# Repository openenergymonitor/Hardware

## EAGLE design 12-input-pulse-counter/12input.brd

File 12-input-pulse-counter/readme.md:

## 12 Input Pulse Counter

**This is a design in development for a 12-input puse counter for interfacing with 12 utility meters.**

Many meters have pulse outputs, including electricity meters: single phase, 3-phase, import, export.. Gas meters, Water flow meters etc

The pulse output may be a flashing LED or a switching relay (usually solid state) or both.

In the case of an electricity meter a pulse output corresponds to a certain amount of energy passing through the meter (Kwhr/Wh). For single-phase domestic electricity meters (eg. Elster A100c) each pulse usually corresponds to 1 Wh (1000 pulses per kwh).  For the case of higher power meters (often three-phase) each pulse corresponds to a greater amount of energy eg. 2whr per pulse or even 10whr per pulse. 

Full introduction to pulse counting: [Building Blocks > Pulse counting](http://openenergymonitor.org/emon/buildingblocks/introduction-to-pulse-counting)

The usual way to do pulse counting on the Arduino is to use the 2 Interrupt pins but this limits us to 2 meters. The following hardware design is for a 12 input arduino based pulse counter that runs firmware that samples all the arduino digital input pins at high sample rate. For full details including arduino source code see: [Building Blocks > 12 input pulse counting](http://openenergymonitor.org/emon/buildingblocks/12-input-pulse-counting)

### Eagle schematic and board file

Download both the schematic and board file and open in eagle, click on File > Switch to Board to navigate between schematic view and PCB Board view.

- Schematic: [12input.sch](12input.sch)
- Board: [12input.brd](12input.brd)

### Schematic

### Board

### Open Hardware

Hardware designs (schematics and CAD) files are licensed under the [Creative Commons Attribution-ShareAlike 3.0 Unported License](http://creativecommons.org/licenses/by-sa/3.0/) and follow the terms of the [OSHW (Open-source hardware) Statement of Principles 1.0.](http://freedomdefined.org/OSHW)

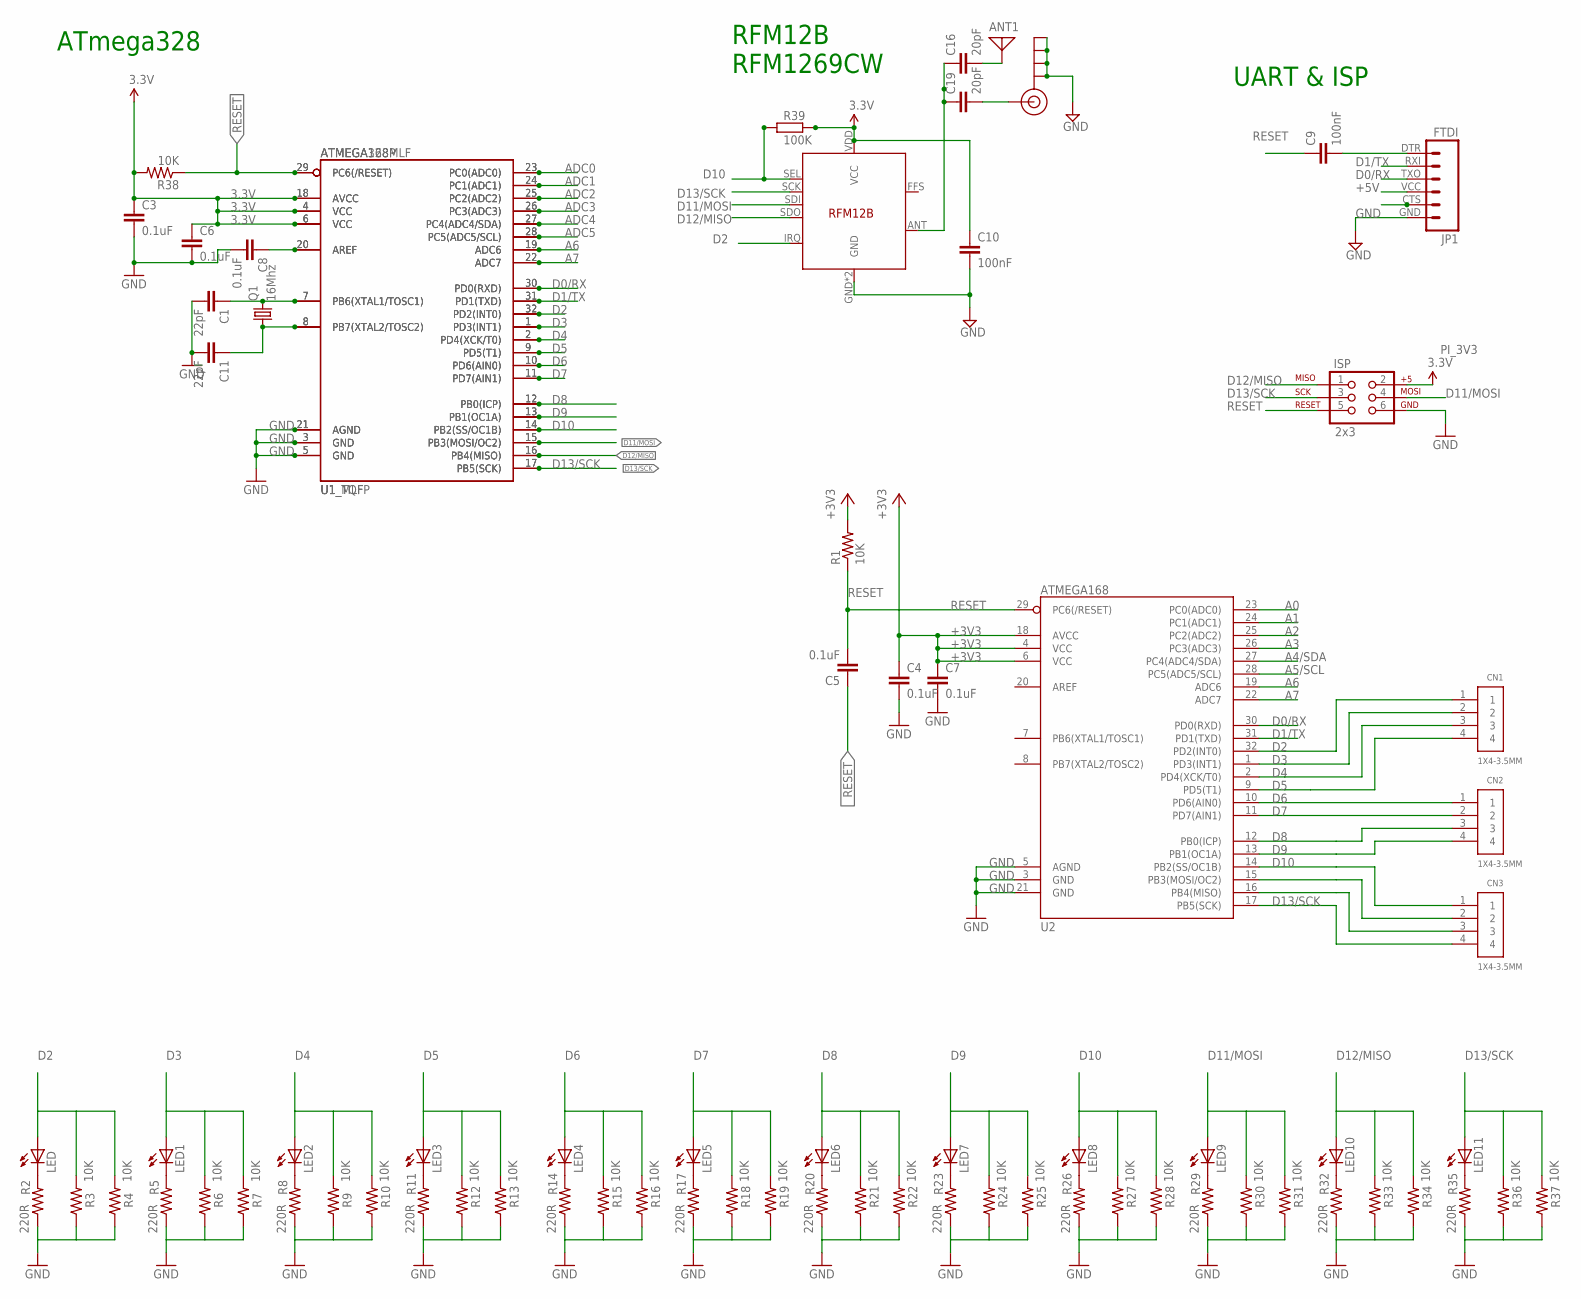
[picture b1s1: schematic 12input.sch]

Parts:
ANT1: ANTENNA; PAD-01
C1, C11: 22pF; C0603
C3, C4, C5, C6, C7, C8: 0.1uF; C0603
C9, C10: 100nF; C0603
C16, C19: 20pF; C0603
CN1, CN2, CN3: 1X4-3.5MM; 1X04-3.5MM
ISP: 2x3; 2X3
J$1: SMA_EDGE; SMA-EDGE
JP1: FTDI; FTDI_BASIC
LED, LED1, LED2, LED3, LED4, LED5, LED6, LED7, LED8, LED9, LED10, LED11: LEDSML0603; SML0603
Q1: 16Mhz; HC49UP
R1, R3, R6, R9, R12, R15, R18, R21, R24, R27, R30, R33, R36, R38: 10K; R0603
R2, R5, R8, R11, R14, R17, R20, R23, R26, R29, R32, R35: 220R; R0603
R4, R7, R10, R13, R16, R19, R22, R25, R28, R31, R34, R37: 10K; 0204/7
R39: 100K; R0603
U1_MLF: ATMEGA168MLF; MLF32
U1_TQFP: ATMEGA328P; TQFP32-08
U2: ATMEGA168; TQFP32-08
U$14: RFM12B

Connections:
3.3V: C3.1, C6.1, C10.1, ISP.2, R38.2, R39.2, U1_MLF.4 (VCC), U1_MLF.6 (VCC), U1_MLF.18 (AVCC), U1_TQFP.4 (VCC), U1_TQFP.6 (VCC), U1_TQFP.18 (AVCC), U$14.VDD (VCC)
+3V3: C4.1, C7.1, R1.2, U2.4 (VCC), U2.6 (VCC), U2.18 (AVCC)
+5V: JP1.VCC (4)
A0: U2.23 (PC0(ADC0))
A1: U2.24 (PC1(ADC1))
A2: U2.25 (PC2(ADC2))
A3: U2.26 (PC3(ADC3))
A4/SDA: U2.27 (PC4(ADC4/SDA))
A5/SCL: U2.28 (PC5(ADC5/SCL))
A6: U1_MLF.19 (ADC6), U1_TQFP.19 (ADC6), U2.19 (ADC6)
A7: U1_MLF.22 (ADC7), U1_TQFP.22 (ADC7), U2.22 (ADC7)
ADC0: U1_MLF.23 (PC0(ADC0)), U1_TQFP.23 (PC0(ADC0))
ADC1: U1_MLF.24 (PC1(ADC1)), U1_TQFP.24 (PC1(ADC1))
ADC2: U1_MLF.25 (PC2(ADC2)), U1_TQFP.25 (PC2(ADC2))
ADC3: U1_MLF.26 (PC3(ADC3)), U1_TQFP.26 (PC3(ADC3))
ADC4: U1_MLF.27 (PC4(ADC4/SDA)), U1_TQFP.27 (PC4(ADC4/SDA))
ADC5: U1_MLF.28 (PC5(ADC5/SCL)), U1_TQFP.28 (PC5(ADC5/SCL))
D0/RX: JP1.TXO (3), U1_MLF.30 (PD0(RXD)), U1_TQFP.30 (PD0(RXD)), U2.30 (PD0(RXD))
D1/TX: JP1.RXI (2), U1_MLF.31 (PD1(TXD)), U1_TQFP.31 (PD1(TXD)), U2.31 (PD1(TXD))
D2: CN1.1, LED.A, R3.2, R4.2, U1_MLF.32 (PD2(INT0)), U1_TQFP.32 (PD2(INT0)), U2.32 (PD2(INT0)), U$14.IRQ
D3: CN1.2, LED1.A, R6.2, R7.2, U1_MLF.1 (PD3(INT1)), U1_TQFP.1 (PD3(INT1)), U2.1 (PD3(INT1))
D4: CN1.3, LED2.A, R9.2, R10.2, U1_MLF.2 (PD4(XCK/T0)), U1_TQFP.2 (PD4(XCK/T0)), U2.2 (PD4(XCK/T0))
D5: CN1.4, LED3.A, R12.2, R13.2, U1_MLF.9 (PD5(T1)), U1_TQFP.9 (PD5(T1)), U2.9 (PD5(T1))
D6: CN2.1, LED4.A, R15.2, R16.2, U1_MLF.10 (PD6(AIN0)), U1_TQFP.10 (PD6(AIN0)), U2.10 (PD6(AIN0))
D7: CN2.2, LED5.A, R18.2, R19.2, U1_MLF.11 (PD7(AIN1)), U1_TQFP.11 (PD7(AIN1)), U2.11 (PD7(AIN1))
D8: CN2.3, LED6.A, R21.2, R22.2, U1_MLF.12 (PB0(ICP)), U1_TQFP.12 (PB0(ICP)), U2.12 (PB0(ICP))
D9: CN2.4, LED7.A, R24.2, R25.2, U1_MLF.13 (PB1(OC1A)), U1_TQFP.13 (PB1(OC1A)), U2.13 (PB1(OC1A))
D10: CN3.1, LED8.A, R27.2, R28.2, R39.1, U1_MLF.14 (PB2(SS/OC1B)), U1_TQFP.14 (PB2(SS/OC1B)), U2.14 (PB2(SS/OC1B)), U$14.SEL
D11/MOSI: CN3.2, ISP.4, LED9.A, R30.2, R31.2, U1_MLF.15 (PB3(MOSI/OC2)), U1_TQFP.15 (PB3(MOSI/OC2)), U2.15 (PB3(MOSI/OC2)), U$14.SDI
D12/MISO: CN3.3, ISP.1, LED10.A, R33.2, R34.2, U1_MLF.16 (PB4(MISO)), U1_TQFP.16 (PB4(MISO)), U2.16 (PB4(MISO)), U$14.SDO
D13/SCK: CN3.4, ISP.3, LED11.A, R36.2, R37.2, U1_MLF.17 (PB5(SCK)), U1_TQFP.17 (PB5(SCK)), U2.17 (PB5(SCK)), U$14.SCK
DIG1: C16.1, C19.1, U$14.ANT
GND: C1.2, C3.2, C4.2, C6.2, C7.2, C8.2, C10.2, C11.2, ISP.6, J$1.GND@0 (GND), J$1.GND@1 (GND), J$1.GND@2 (GND), J$1.GND@3 (GND), JP1.GND (6), R2.1, R3.1, R4.1, R5.1, R6.1, R7.1, R8.1, R9.1, R10.1, R11.1, R12.1, R13.1, R14.1, R15.1, R16.1, R17.1, R18.1, R19.1, R20.1, R21.1, R22.1, R23.1, R24.1, R25.1, R26.1, R27.1, R28.1, R29.1, R30.1, R31.1, R32.1, R33.1, R34.1, R35.1, R36.1, R37.1, U1_MLF.3 (GND), U1_MLF.5 (GND), U1_MLF.21 (AGND), U1_TQFP.3 (GND), U1_TQFP.5 (GND), U1_TQFP.21 (AGND), U2.3 (GND), U2.5 (AGND), U2.21 (GND), U$14.GND, U$14.P$12 (GND)
unnamed: C1.1, Q1.2, U1_MLF.7 (PB6(XTAL1/TOSC1)), U1_TQFP.7 (PB6(XTAL1/TOSC1))
unnamed: LED1.C, R5.2
unnamed: LED.C, R2.2
unnamed: C11.1, Q1.1, U1_MLF.8 (PB7(XTAL2/TOSC2)), U1_TQFP.8 (PB7(XTAL2/TOSC2))
unnamed: ANT1.1, C16.2
unnamed: LED2.C, R8.2
unnamed: C9.2, JP1.DTR (1)
unnamed: LED3.C, R11.2
unnamed: LED4.C, R14.2
unnamed: LED5.C, R17.2
unnamed: LED6.C, R20.2
unnamed: LED7.C, R23.2
unnamed: LED8.C, R26.2
unnamed: C8.1, U1_MLF.20 (AREF), U1_TQFP.20 (AREF)
unnamed: LED9.C, R29.2
unnamed: LED10.C, R32.2
unnamed: C19.2, J$1.SIG (SIGNAL)
unnamed: LED11.C, R35.2
RESET: C5.2, C9.1, ISP.5, R1.1, R38.1, U1_MLF.29 (PC6(/RESET)), U1_TQFP.29 (PC6(/RESET)), U2.29 (PC6(/RESET))
_RESET: C5.1

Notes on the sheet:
ATmega328
RFM12B RFM1269CW
UART & ISP

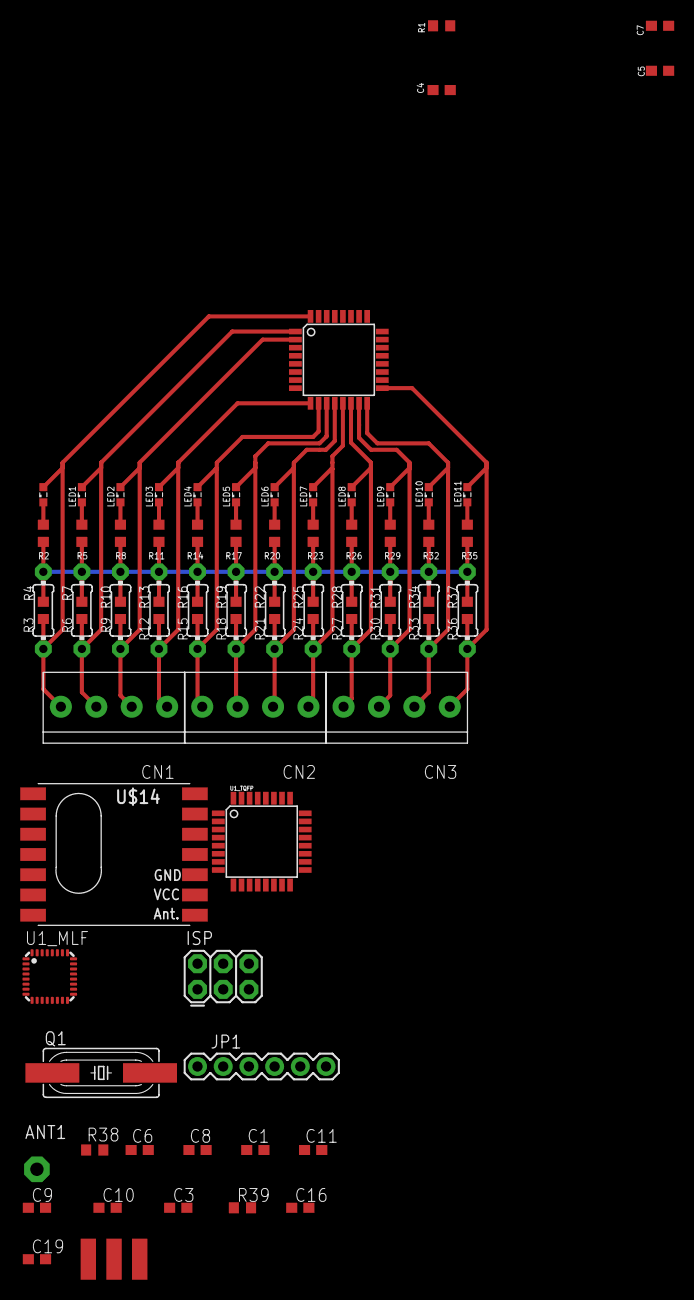
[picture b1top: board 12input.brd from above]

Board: 2 copper layers, 76 parts (1 on the bottom side), 45 nets.

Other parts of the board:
U$4: OSHW_6X200_NOTEXT

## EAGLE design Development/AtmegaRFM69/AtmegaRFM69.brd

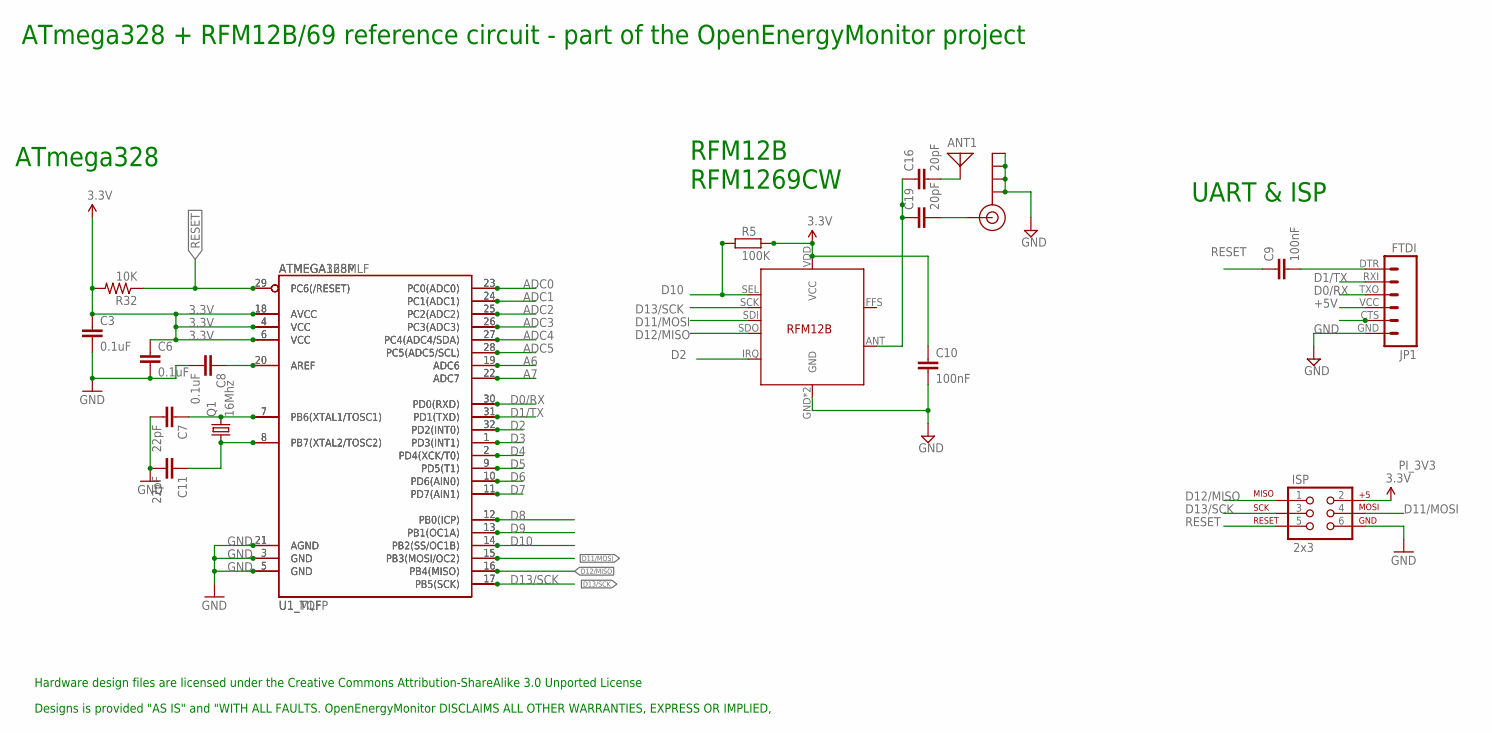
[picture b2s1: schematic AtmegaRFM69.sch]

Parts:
ANT1: ANTENNA; PAD-01
C3, C6, C8: 0.1uF; C0603
C7, C11: 22pF; C0603
C9, C10: 100nF; C0603
C16, C19: 20pF; C0603
ISP: 2x3; 2X3
J$1: SMA_EDGE; SMA-EDGE
JP1: FTDI; FTDI_BASIC
Q1: 16Mhz; HC49UP
R5: 100K; R0603
R32: 10K; R0603
U1_MLF: ATMEGA168MLF; MLF32
U1_TQFP: ATMEGA328P; TQFP32-08
U$14: RFM12B

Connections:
3.3V: C3.1, C6.1, C10.1, ISP.2, R5.2, R32.2, U1_MLF.4 (VCC), U1_MLF.6 (VCC), U1_MLF.18 (AVCC), U1_TQFP.4 (VCC), U1_TQFP.6 (VCC), U1_TQFP.18 (AVCC), U$14.VDD (VCC)
+5V: JP1.VCC (4)
A6: U1_MLF.19 (ADC6), U1_TQFP.19 (ADC6)
A7: U1_MLF.22 (ADC7), U1_TQFP.22 (ADC7)
ADC0: U1_MLF.23 (PC0(ADC0)), U1_TQFP.23 (PC0(ADC0))
ADC1: U1_MLF.24 (PC1(ADC1)), U1_TQFP.24 (PC1(ADC1))
ADC2: U1_MLF.25 (PC2(ADC2)), U1_TQFP.25 (PC2(ADC2))
ADC3: U1_MLF.26 (PC3(ADC3)), U1_TQFP.26 (PC3(ADC3))
ADC4: U1_MLF.27 (PC4(ADC4/SDA)), U1_TQFP.27 (PC4(ADC4/SDA))
ADC5: U1_MLF.28 (PC5(ADC5/SCL)), U1_TQFP.28 (PC5(ADC5/SCL))
D0/RX: JP1.TXO (3), U1_MLF.30 (PD0(RXD)), U1_TQFP.30 (PD0(RXD))
D1/TX: JP1.RXI (2), U1_MLF.31 (PD1(TXD)), U1_TQFP.31 (PD1(TXD))
D2: U1_MLF.32 (PD2(INT0)), U1_TQFP.32 (PD2(INT0)), U$14.IRQ
D3: U1_MLF.1 (PD3(INT1)), U1_TQFP.1 (PD3(INT1))
D4: U1_MLF.2 (PD4(XCK/T0)), U1_TQFP.2 (PD4(XCK/T0))
D5: U1_MLF.9 (PD5(T1)), U1_TQFP.9 (PD5(T1))
D6: U1_MLF.10 (PD6(AIN0)), U1_TQFP.10 (PD6(AIN0))
D7: U1_MLF.11 (PD7(AIN1)), U1_TQFP.11 (PD7(AIN1))
D8: U1_MLF.12 (PB0(ICP)), U1_TQFP.12 (PB0(ICP))
D9: U1_MLF.13 (PB1(OC1A)), U1_TQFP.13 (PB1(OC1A))
D10: R5.1, U1_MLF.14 (PB2(SS/OC1B)), U1_TQFP.14 (PB2(SS/OC1B)), U$14.SEL
D11/MOSI: ISP.4, U1_MLF.15 (PB3(MOSI/OC2)), U1_TQFP.15 (PB3(MOSI/OC2)), U$14.SDI
D12/MISO: ISP.1, U1_MLF.16 (PB4(MISO)), U1_TQFP.16 (PB4(MISO)), U$14.SDO
D13/SCK: ISP.3, U1_MLF.17 (PB5(SCK)), U1_TQFP.17 (PB5(SCK)), U$14.SCK
DIG1: C16.1, C19.1, U$14.ANT
GND: C3.2, C6.2, C7.2, C8.2, C10.2, C11.2, ISP.6, J$1.GND@0 (GND), J$1.GND@1 (GND), J$1.GND@2 (GND), J$1.GND@3 (GND), JP1.GND (6), U1_MLF.3 (GND), U1_MLF.5 (GND), U1_MLF.21 (AGND), U1_TQFP.3 (GND), U1_TQFP.5 (GND), U1_TQFP.21 (AGND), U$14.GND, U$14.P$12 (GND)
unnamed: C7.1, Q1.2, U1_MLF.7 (PB6(XTAL1/TOSC1)), U1_TQFP.7 (PB6(XTAL1/TOSC1))
unnamed: C11.1, Q1.1, U1_MLF.8 (PB7(XTAL2/TOSC2)), U1_TQFP.8 (PB7(XTAL2/TOSC2))
unnamed: ANT1.1, C16.2
unnamed: C8.1, U1_MLF.20 (AREF), U1_TQFP.20 (AREF)
unnamed: C9.2, JP1.DTR (1)
unnamed: C19.2, J$1.SIG (SIGNAL)
RESET: C9.1, ISP.5, R32.1, U1_MLF.29 (PC6(/RESET)), U1_TQFP.29 (PC6(/RESET))

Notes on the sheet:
ATmega328
RFM12B RFM1269CW
Hardware design files are licensed under the Creative Commons Attribution-ShareAlike 3.0 Unported License
Designs is provided "AS IS" and "WITH ALL FAULTS. OpenEnergyMonitor DISCLAIMS ALL OTHER WARRANTIES, EXPRESS OR IMPLIED,
ATmega328 + RFM12B/69 reference circuit - part of the OpenEnergyMonitor project
UART & ISP

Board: 2 copper layers, 19 parts (0 on the bottom side), 32 nets, no tracks yet.

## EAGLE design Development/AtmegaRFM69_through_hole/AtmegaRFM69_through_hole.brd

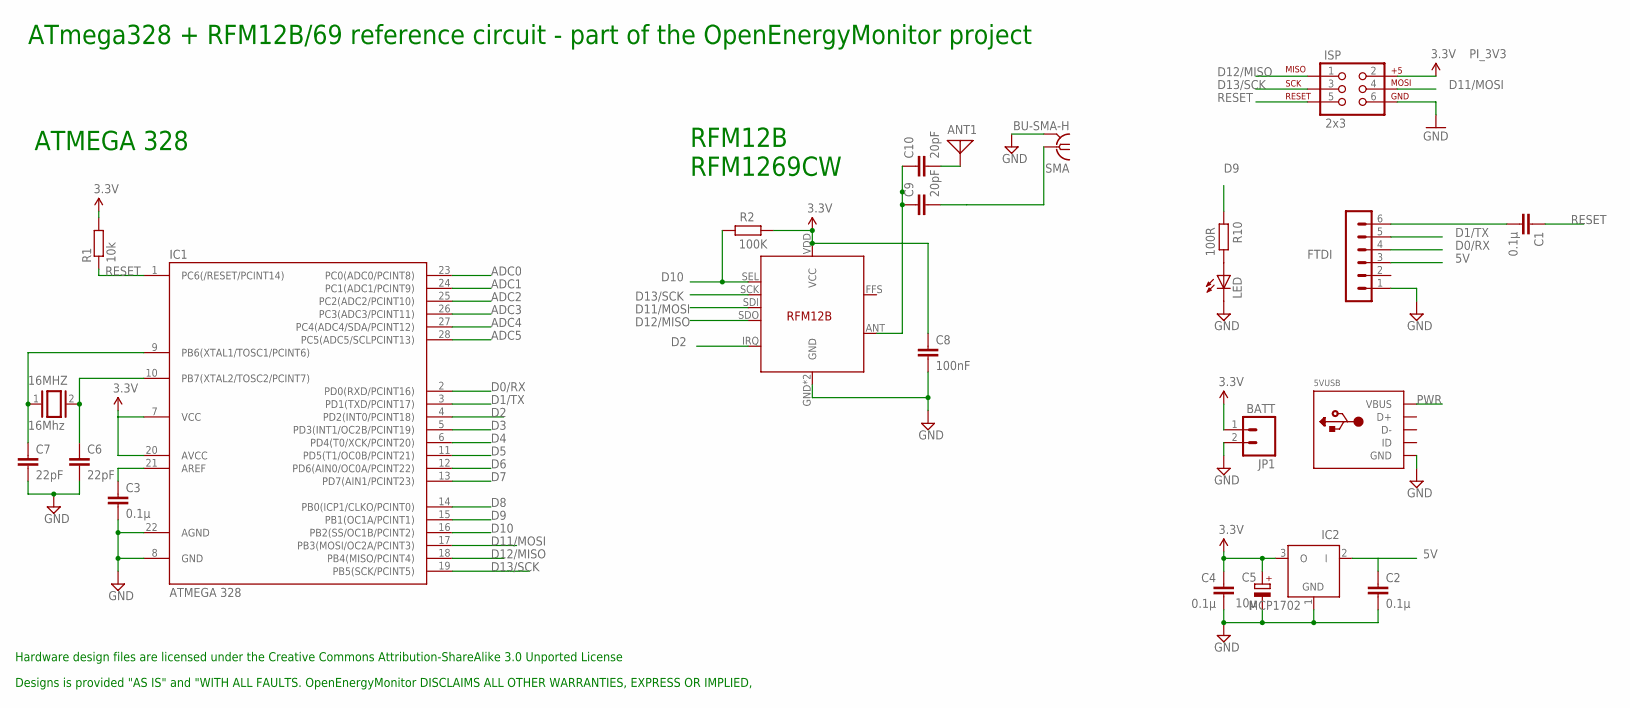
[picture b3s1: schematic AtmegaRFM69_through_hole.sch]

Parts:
5VUSB: USBMOLEX; USB-MINIB-THM-MOLEX
16MHZ: 16Mhz; QS
ANT1: ANTENNA; PAD-01
C1, C2, C3, C4: 0.1µ; C025-024X044
C5: 10µ; E1,8-4
C6, C7: 22pF; C2.5-2
C8: 100nF; C025-024X044
C9, C10: 20pF; C025-024X044
FTDI: FTDI; MA06-1
IC1: ATMEGA 328; DIL28-3
IC2: MCP1702; TO92
ISP: 2x3; 2X3
JP1: BATT; 1X02_LOCK_LONGPADS
LED: LED3MM
R1: 10k; 0204/7
R2: 100K; 0204/7
R10: 100R; 0204/7
SMA: BU-SMA-H
U$14: RFM12B

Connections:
3.3V: C4.1, C5.+, C8.1, IC1.7 (VCC), IC1.20 (AVCC), IC2.3 (O), ISP.2, JP1.1, R1.2, R2.1, U$14.VDD (VCC)
5V: C2.1, FTDI.3, IC2.2 (I)
ADC0: IC1.23 (PC0(ADC0/PCINT8))
ADC1: IC1.24 (PC1(ADC1/PCINT9))
ADC2: IC1.25 (PC2(ADC2/PCINT10))
ADC3: IC1.26 (PC3(ADC3/PCINT11))
ADC4: IC1.27 (PC4(ADC4/SDA/PCINT12))
ADC5: IC1.28 (PC5(ADC5/SCLPCINT13))
D0/RX: FTDI.4, IC1.2 (PD0(RXD/PCINT16))
D1/TX: FTDI.5, IC1.3 (PD1(TXD/PCINT17))
D2: IC1.4 (PD2(INT0/PCINT18)), U$14.IRQ
D3: IC1.5 (PD3(INT1/OC2B/PCINT19))
D4: IC1.6 (PD4(T0/XCK/PCINT20))
D5: IC1.11 (PD5(T1/OC0B/PCINT21))
D6: IC1.12 (PD6(AIN0/OC0A/PCINT22))
D7: IC1.13 (PD7(AIN1/PCINT23))
D8: IC1.14 (PB0(ICP1/CLKO/PCINT0))
D9: IC1.15 (PB1(OC1A/PCINT1)), R10.2
D10: IC1.16 (PB2(SS/OC1B/PCINT2)), R2.2, U$14.SEL
D11/MOSI: IC1.17 (PB3(MOSI/OC2A/PCINT3)), ISP.4, U$14.SDI
D12/MISO: IC1.18 (PB4(MISO/PCINT4)), ISP.1, U$14.SDO
D13/SCK: IC1.19 (PB5(SCK/PCINT5)), ISP.3, U$14.SCK
DIG1: C9.1, C10.1, U$14.ANT
GND: 5VUSB.GND, C2.2, C3.2, C4.2, C5.-, C6.2, C7.2, C8.2, FTDI.1, IC1.8 (GND), IC1.22 (AGND), IC2.1 (GND), ISP.6, JP1.2, LED.K (C), SMA.2, SMA.3 (2), SMA.4 (2), SMA.5 (2), U$14.GND, U$14.P$12 (GND)
unnamed: 16MHZ.2, C6.1, IC1.10 (PB7(XTAL2/TOSC2/PCINT7))
unnamed: LED.A, R10.1
unnamed: ANT1.1, C10.2
unnamed: 16MHZ.1, C7.1, IC1.9 (PB6(XTAL1/TOSC1/PCINT6))
unnamed: C1.2, FTDI.6
unnamed: C3.1, IC1.21 (AREF)
unnamed: C9.2, SMA.1
PWR: 5VUSB.VBUS
RESET: C1.1, IC1.1 (PC6(/RESET/PCINT14)), ISP.5, R1.1

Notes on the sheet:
RFM12B RFM1269CW
ATMEGA 328
Hardware design files are licensed under the Creative Commons Attribution-ShareAlike 3.0 Unported License
Designs is provided "AS IS" and "WITH ALL FAULTS. OpenEnergyMonitor DISCLAIMS ALL OTHER WARRANTIES, EXPRESS OR IMPLIED,
ATmega328 + RFM12B/69 reference circuit - part of the OpenEnergyMonitor project

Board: 2 copper layers, 24 parts (0 on the bottom side), 20 nets, no tracks yet.

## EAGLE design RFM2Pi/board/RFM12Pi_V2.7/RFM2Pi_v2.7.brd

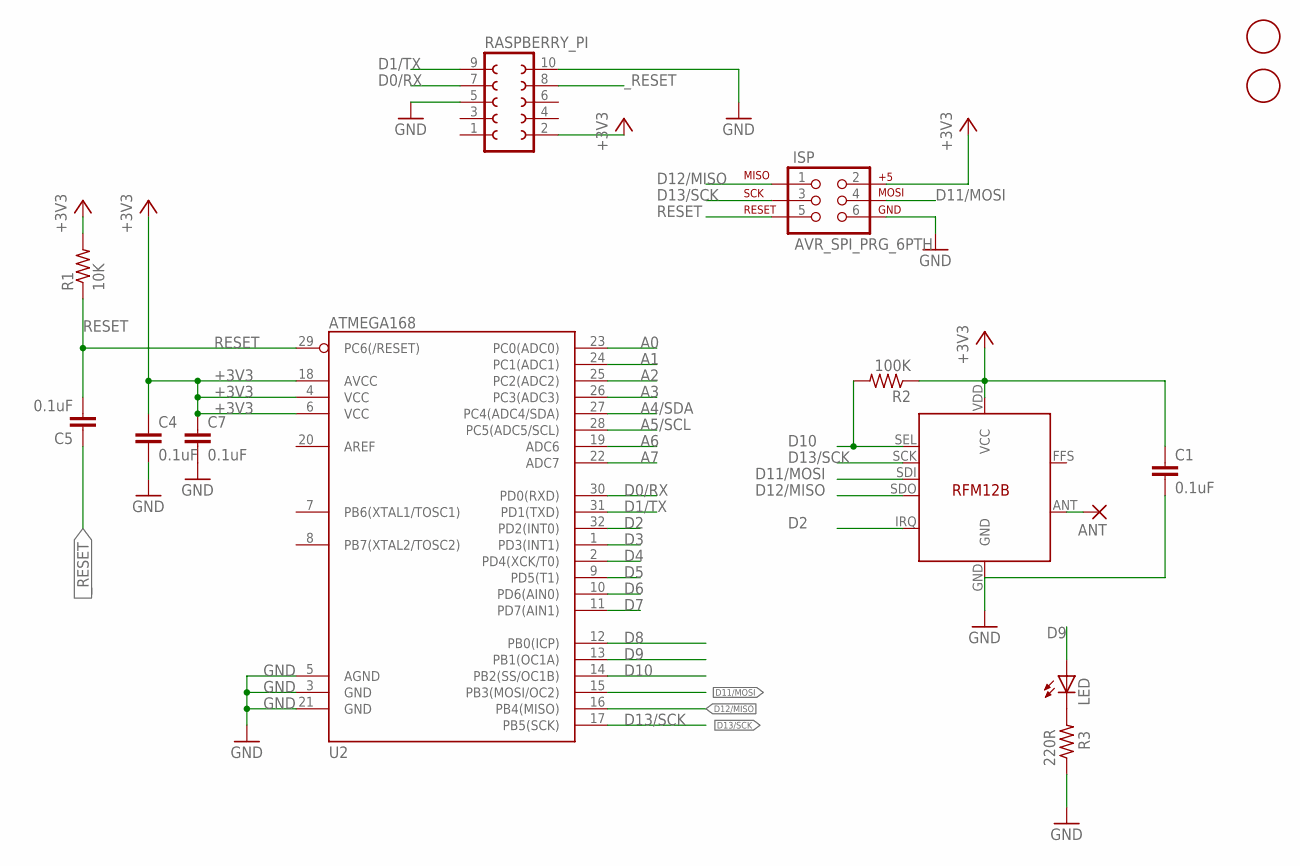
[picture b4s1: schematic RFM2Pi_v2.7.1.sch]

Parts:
ANT: 1,6/0,8
C1, C4, C5, C7: 0.1uF; C0603
ISP: AVR_SPI_PRG_6PTH; 2X3
LED: LEDSML0603; SML0603
R1: 10K; R0603
R2: 100K; R0603
R3: 220R; R0603
RASPBERRY_PI: FE05-2
RFM12B: RFM12B
U2: ATMEGA168; TQFP32-08
U$1, U$2: FIDUCIAL; FIDUCIAL_1MM

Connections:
+3V3: C1.1, C4.1, C7.1, ISP.2, R1.2, R2.1, RASPBERRY_PI.2, RFM12B.VDD (VCC), U2.4 (VCC), U2.6 (VCC), U2.18 (AVCC)
A0: U2.23 (PC0(ADC0))
A1: U2.24 (PC1(ADC1))
A2: U2.25 (PC2(ADC2))
A3: U2.26 (PC3(ADC3))
A4/SDA: U2.27 (PC4(ADC4/SDA))
A5/SCL: U2.28 (PC5(ADC5/SCL))
A6: U2.19 (ADC6)
A7: U2.22 (ADC7)
D0/RX: RASPBERRY_PI.7, U2.30 (PD0(RXD))
D1/TX: RASPBERRY_PI.9, U2.31 (PD1(TXD))
D2: RFM12B.IRQ, U2.32 (PD2(INT0))
D3: U2.1 (PD3(INT1))
D4: U2.2 (PD4(XCK/T0))
D5: U2.9 (PD5(T1))
D6: U2.10 (PD6(AIN0))
D7: U2.11 (PD7(AIN1))
D8: U2.12 (PB0(ICP))
D9: LED.A, U2.13 (PB1(OC1A))
D10: R2.2, RFM12B.SEL, U2.14 (PB2(SS/OC1B))
D11/MOSI: ISP.4, RFM12B.SDI, U2.15 (PB3(MOSI/OC2))
D12/MISO: ISP.1, RFM12B.SDO, U2.16 (PB4(MISO))
D13/SCK: ISP.3, RFM12B.SCK, U2.17 (PB5(SCK))
GND: C1.2, C4.2, C7.2, ISP.6, R3.1, RASPBERRY_PI.5, RASPBERRY_PI.10, RFM12B.GND, U2.3 (GND), U2.5 (AGND), U2.21 (GND)
unnamed: LED.C, R3.2
unnamed: ANT.1, RFM12B.ANT
RESET: C5.2, ISP.5, R1.1, U2.29 (PC6(/RESET))
_RESET: C5.1, RASPBERRY_PI.8

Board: 2 copper layers, 15 parts (0 on the bottom side), 14 nets, no tracks yet.

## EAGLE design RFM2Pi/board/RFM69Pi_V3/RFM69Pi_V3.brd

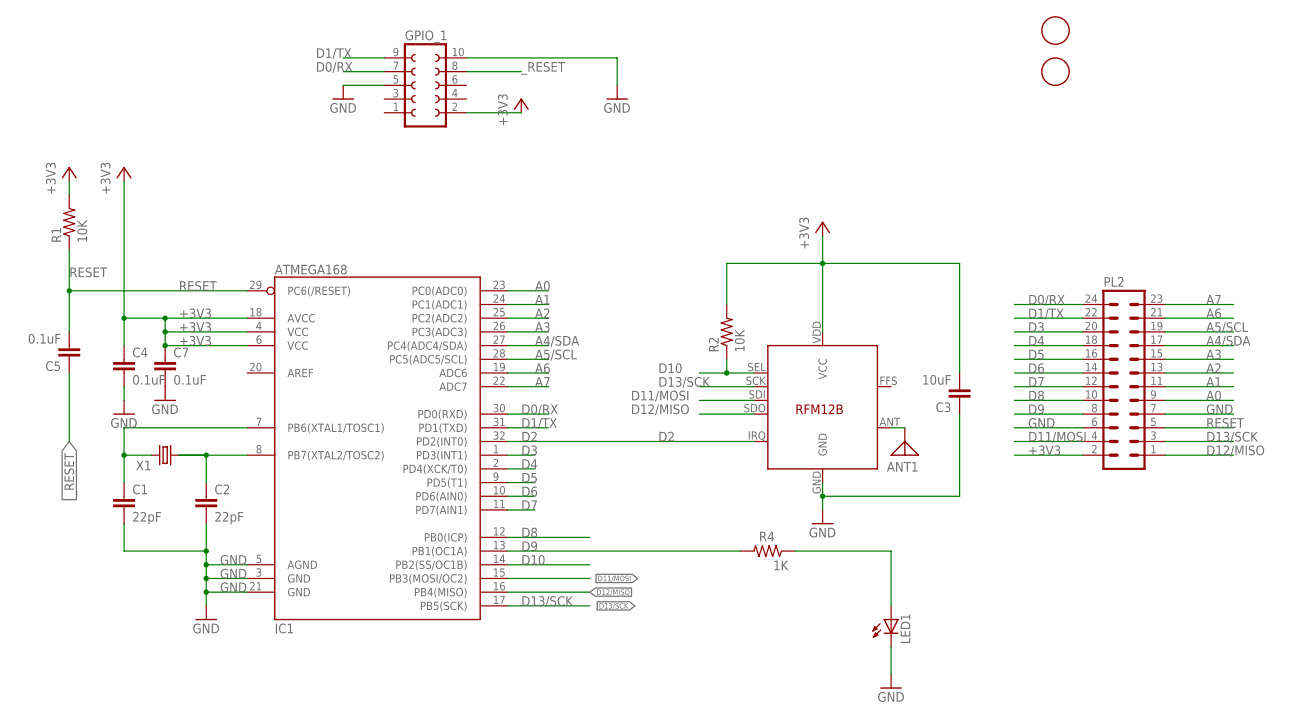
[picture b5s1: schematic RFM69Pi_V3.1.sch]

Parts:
ANT1: ANTENNA; PAD-01
C1, C2: 22pF; C0603
C3: 10uF; C0603
C4, C5, C7: 0.1uF; C0603
GPIO_1: FE05-2
IC1: ATMEGA168; TQFP32-08
LED1: LEDSML0603; SML0603
PL2: MA12-2
R1, R2: 10K; R0603
R4: 1K; R0603
RFM12B-RFM69CW: RFM12B
U$1, U$2: FIDUCIAL; FIDUCIAL_1MM
X1: CRYSTALHC49US; HC49US

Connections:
+3V3: C3.2, C4.1, C7.1, GPIO_1.2, IC1.4 (VCC), IC1.6 (VCC), IC1.18 (AVCC), PL2.2, R1.2, R2.2, RFM12B-RFM69CW.VDD (VCC)
A0: IC1.23 (PC0(ADC0)), PL2.9
A1: IC1.24 (PC1(ADC1)), PL2.11
A2: IC1.25 (PC2(ADC2)), PL2.13
A3: IC1.26 (PC3(ADC3)), PL2.15
A4/SDA: IC1.27 (PC4(ADC4/SDA)), PL2.17
A5/SCL: IC1.28 (PC5(ADC5/SCL)), PL2.19
A6: IC1.19 (ADC6), PL2.21
A7: IC1.22 (ADC7), PL2.23
D0/RX: GPIO_1.7, IC1.30 (PD0(RXD)), PL2.24
D1/TX: GPIO_1.9, IC1.31 (PD1(TXD)), PL2.22
D2: IC1.32 (PD2(INT0)), RFM12B-RFM69CW.IRQ
D3: IC1.1 (PD3(INT1)), PL2.20
D4: IC1.2 (PD4(XCK/T0)), PL2.18
D5: IC1.9 (PD5(T1)), PL2.16
D6: IC1.10 (PD6(AIN0)), PL2.14
D7: IC1.11 (PD7(AIN1)), PL2.12
D8: IC1.12 (PB0(ICP)), PL2.10
D9: IC1.13 (PB1(OC1A)), PL2.8, R4.2
D10: IC1.14 (PB2(SS/OC1B)), R2.1, RFM12B-RFM69CW.SEL
D11/MOSI: IC1.15 (PB3(MOSI/OC2)), PL2.4, RFM12B-RFM69CW.SDI
D12/MISO: IC1.16 (PB4(MISO)), PL2.1, RFM12B-RFM69CW.SDO
D13/SCK: IC1.17 (PB5(SCK)), PL2.3, RFM12B-RFM69CW.SCK
GND: C1.2, C2.2, C3.1, C4.2, C7.2, GPIO_1.5, GPIO_1.10, IC1.3 (GND), IC1.5 (AGND), IC1.21 (GND), LED1.C, PL2.6, PL2.7, RFM12B-RFM69CW.GND
unnamed: C1.1, IC1.7 (PB6(XTAL1/TOSC1)), X1.2
unnamed: C2.1, IC1.8 (PB7(XTAL2/TOSC2)), X1.1
unnamed: LED1.A, R4.1
unnamed 27: ANT1.1, RFM12B-RFM69CW.ANT; also elsewhere on the board
RESET: C5.2, IC1.29 (PC6(/RESET)), PL2.5, R1.1
_RESET: C5.1, GPIO_1.8

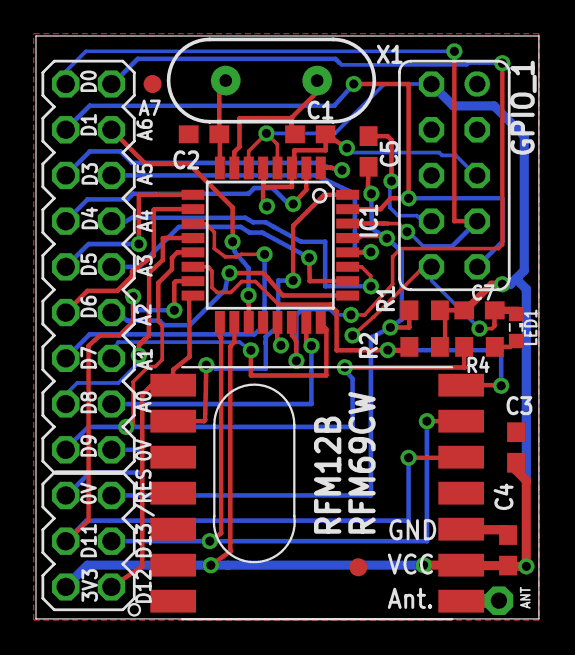
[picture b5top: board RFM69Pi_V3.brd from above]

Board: 2 copper layers, 27.9 x 32.4 mm, 18 parts (0 on the bottom side), 30 nets.

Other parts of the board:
ANT: 1,6/0,8

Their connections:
unnamed 27: ANT.1; also elsewhere on the board

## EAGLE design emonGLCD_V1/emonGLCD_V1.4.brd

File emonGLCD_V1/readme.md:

### Moved to: https://github.com/openenergymonitor/EmonGLCD

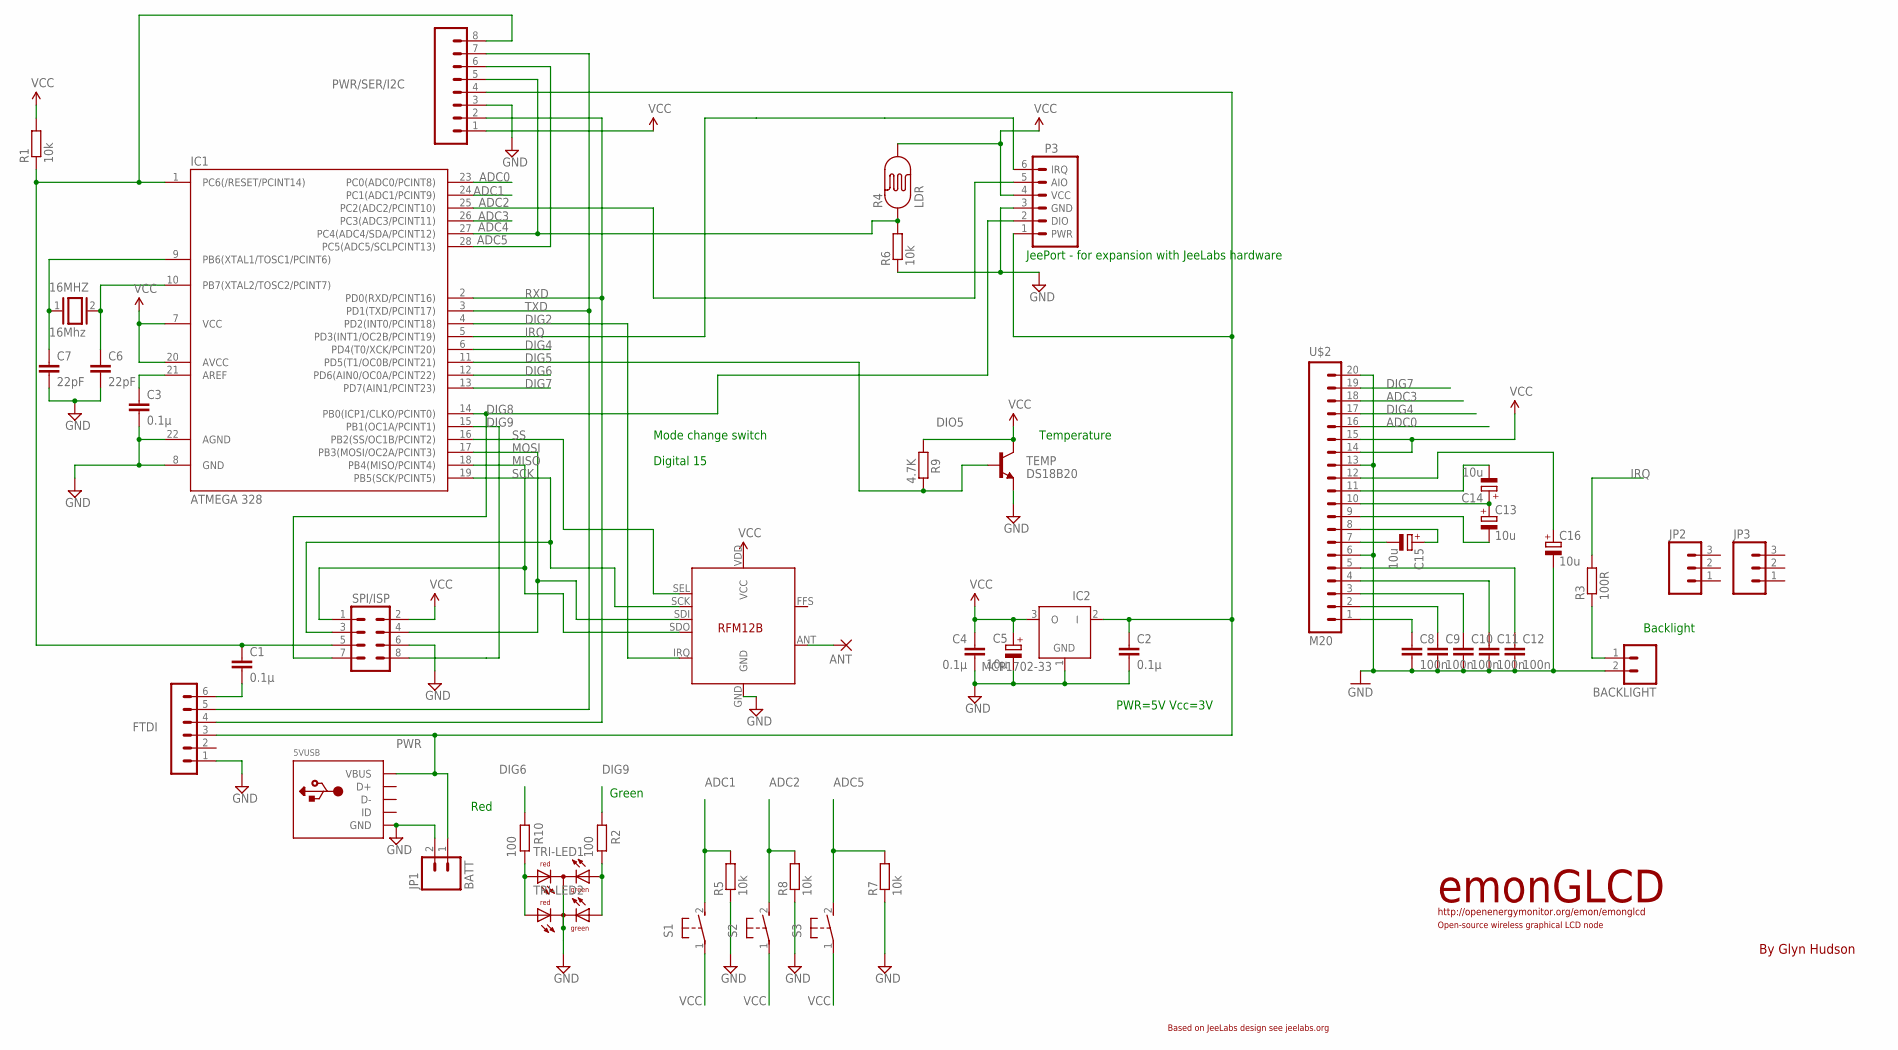
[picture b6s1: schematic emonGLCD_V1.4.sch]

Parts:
5VUSB: USBMOLEX; USB-MINIB-THM-MOLEX
16MHZ: 16Mhz; QS
ANT: 1,6/0,8
BACKLIGHT: M02PTH; 1X02
C1, C2, C3, C4: 0.1µ; C025-024X044
C5: 10µ; E1,8-4
C6, C7: 22pF; C2.5-2
C8, C9, C10, C11, C12: 100n; C2.5-2
C13, C14, C15, C16: 10u; E1,8-4
FTDI: FTDI; MA06-1
IC1: ATMEGA 328; DIL28-3
IC2: MCP1702-33; TO92
JP1: BATT; 1X02_LOCK_LONGPADS
JP2, JP3: M03PTH; 1X03
P3: JEEPORT; PORT6PIN
PWR/SER/I2C: M08; 1X08
R1, R5, R6, R7, R8: 10k; 0204/7
R2, R10: 100; 0204/7
R3: 100R; 0204/7
R4: LDR; PHOTOCELL
R9: 4.7K; 0204/7
S1, S2, S3: 31-XX; B3F-31XX
SV7: SPI/ISP; MA04-2
TEMP: DS18B20; TO-92
TRI-LED1, TRI-LED2: DUOLED5MM
U$1: RFM12B
U$2: M20; 1X20

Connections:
ADC0: IC1.23 (PC0(ADC0/PCINT8)), U$2.16
ADC1: IC1.24 (PC1(ADC1/PCINT9)), R5.2, S1.2 (S)
ADC2: IC1.25 (PC2(ADC2/PCINT10)), P3.5 (AIO), R8.2, S2.2 (S)
ADC3: IC1.26 (PC3(ADC3/PCINT11)), U$2.18
ADC4: IC1.27 (PC4(ADC4/SDA/PCINT12)), PWR/SER/I2C.5, R4.1, R6.2
ADC5: IC1.28 (PC5(ADC5/SCLPCINT13)), PWR/SER/I2C.6, R7.2, S3.2 (S)
DIG2: IC1.4 (PD2(INT0/PCINT18)), U$1.IRQ
DIG4: IC1.6 (PD4(T0/XCK/PCINT20)), U$2.17
DIG5: IC1.11 (PD5(T1/OC0B/PCINT21)), R9.2, TEMP.2 (B)
DIG6: IC1.12 (PD6(AIN0/OC0A/PCINT22)), R10.2
DIG7: IC1.13 (PD7(AIN1/PCINT23)), U$2.19
DIG8: IC1.14 (PB0(ICP1/CLKO/PCINT0)), P3.2 (DIO), SV7.7
DIG9: IC1.15 (PB1(OC1A/PCINT1)), R2.2, SV7.8
GND: 5VUSB.GND, BACKLIGHT.2, C2.2, C3.2, C4.2, C5.-, C6.2, C7.2, C8.2, C9.2, C10.2, C11.2, C12.2, C16.-, FTDI.1, IC1.8 (GND), IC1.22 (AGND), IC2.1 (GND), JP1.2, P3.3 (GND), PWR/SER/I2C.3, R5.1, R6.1, R7.1, R8.1, SV7.6, TEMP.1 (E), TRI-LED1.K (C), TRI-LED2.K (C), U$1.GND, U$2.6, U$2.13, U$2.20
IRQ: IC1.5 (PD3(INT1/OC2B/PCINT19)), P3.6 (IRQ), R3.2
MISO: IC1.18 (PB4(MISO/PCINT4)), SV7.1, U$1.SDO
MOSI: IC1.17 (PB3(MOSI/OC2A/PCINT3)), SV7.4, U$1.SDI
unnamed: 16MHZ.2, C6.1, IC1.10 (PB7(XTAL2/TOSC2/PCINT7))
unnamed: C8.1, U$2.1
unnamed: C9.1, U$2.2
unnamed: C10.1, U$2.3
unnamed: C11.1, U$2.4
unnamed: C12.1, U$2.5
unnamed: R10.1, TRI-LED1.AR, TRI-LED2.AR
unnamed: 16MHZ.1, C7.1, IC1.9 (PB6(XTAL1/TOSC1/PCINT6))
unnamed: ANT.1, U$1.ANT
unnamed: R2.1, TRI-LED1.AG, TRI-LED2.AG
unnamed: C1.2, FTDI.6
unnamed: BACKLIGHT.1, R3.1
unnamed: C3.1, IC1.21 (AREF)
unnamed: C14.-, U$2.11
unnamed: C13.+, C14.+, U$2.10
unnamed: C13.-, U$2.9
unnamed: C15.-, U$2.7
unnamed: C15.+, U$2.8
unnamed: C16.+, U$2.12
PWR: 5VUSB.VBUS, C2.1, FTDI.3, IC2.2 (I), JP1.1, P3.1 (PWR), PWR/SER/I2C.4
RST: C1.1, IC1.1 (PC6(/RESET/PCINT14)), PWR/SER/I2C.8, R1.1, SV7.5
RXD: FTDI.4, IC1.2 (PD0(RXD/PCINT16)), PWR/SER/I2C.2
SCK: IC1.19 (PB5(SCK/PCINT5)), SV7.3, U$1.SCK
SS: IC1.16 (PB2(SS/OC1B/PCINT2)), U$1.SEL
TXD: FTDI.5, IC1.3 (PD1(TXD/PCINT17)), PWR/SER/I2C.7
VCC: C4.1, C5.+, IC1.7 (VCC), IC1.20 (AVCC), IC2.3 (O), P3.4 (VCC), PWR/SER/I2C.1, R1.2, R4.2, R9.1, S1.1, S2.1, S3.1, SV7.2, TEMP.3 (C), U$1.VDD (VCC), U$2.14, U$2.15

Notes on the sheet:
PWR=5V Vcc=3V
Temperature
http://openenergymonitor.org/emon/emonglcd
Open-source wireless graphical LCD node
emonGLCD
By Glyn Hudson
Based on JeeLabs design see jeelabs.org
DIO5
Backlight
Mode change switch
Digital 15
JeePort - for expansion with JeeLabs hardware
Red
Green

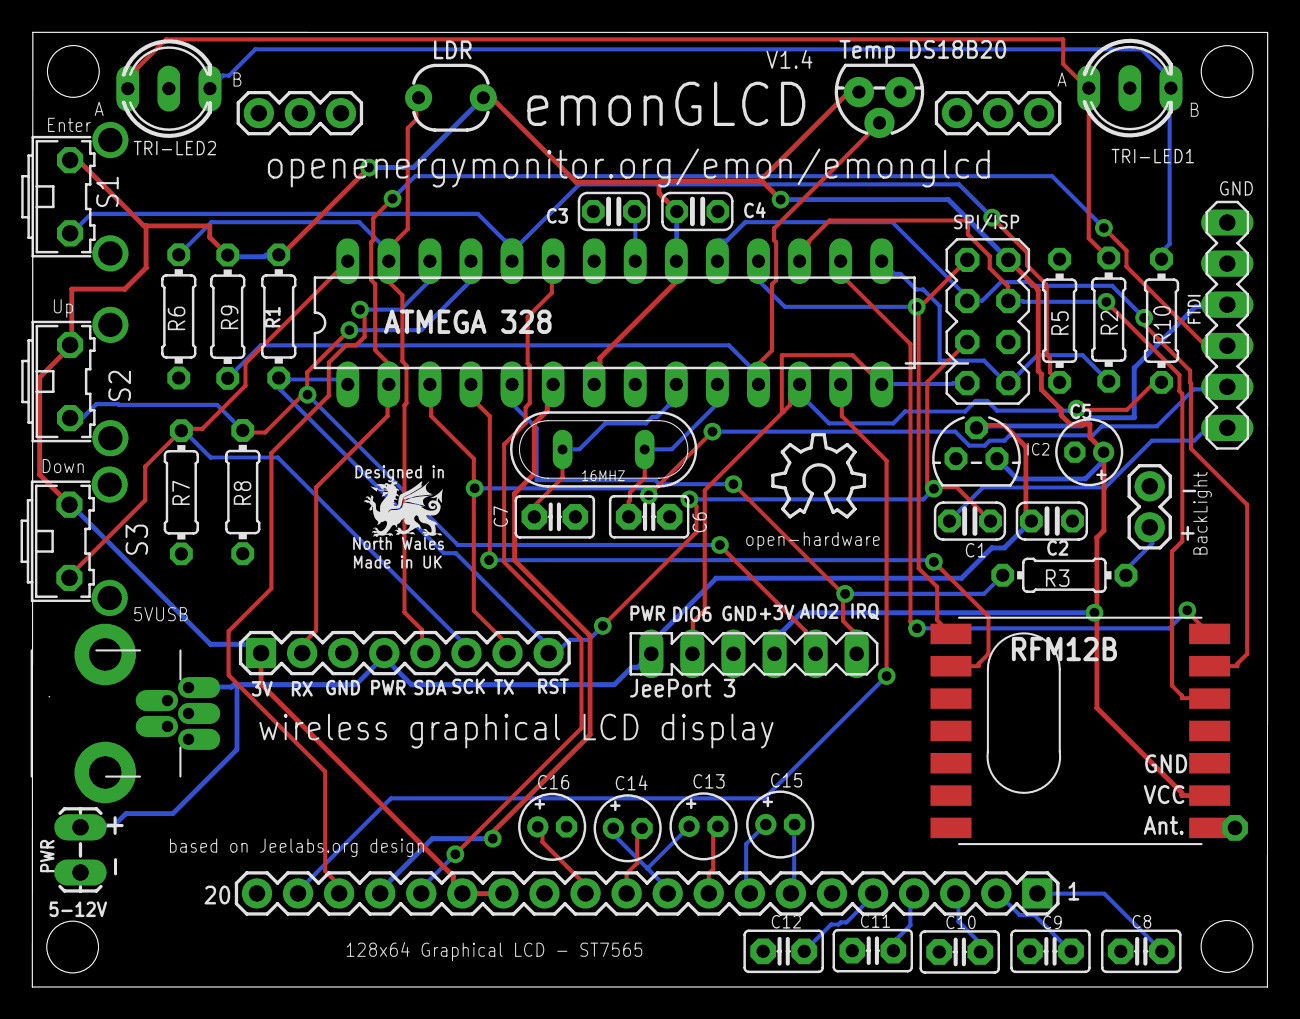
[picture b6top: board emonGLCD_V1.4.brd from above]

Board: 2 copper layers, 76.4 x 59.0 mm, 48 parts (1 on the bottom side), 43 nets.

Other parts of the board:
U$3: Open-source Hardware; OSHW_8X200_NOTEXT

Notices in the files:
parts and their libraries:
SparkFun-DigitalIC: Licensing: CC v3.0 Share-Alike You are welcome to use this library for commercial purposes.
